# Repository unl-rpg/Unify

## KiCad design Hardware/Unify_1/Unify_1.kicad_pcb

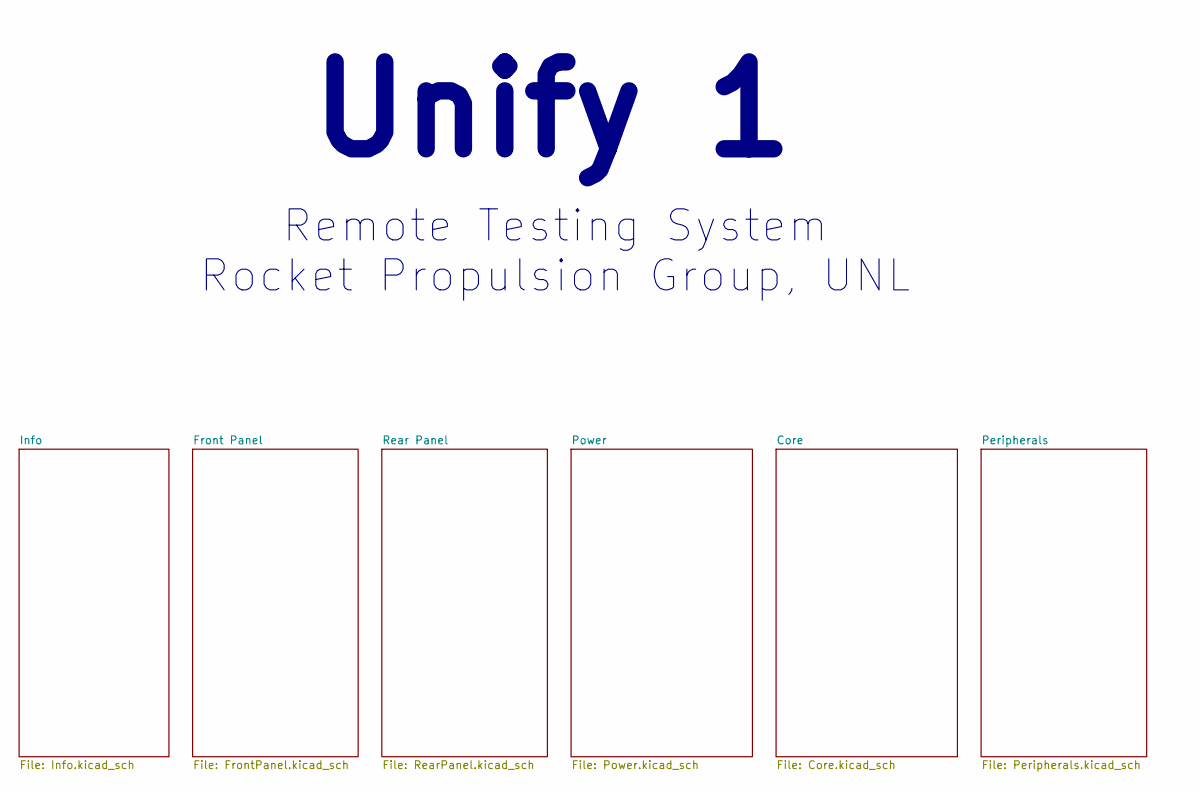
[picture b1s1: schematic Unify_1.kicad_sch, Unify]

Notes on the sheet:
Unify 1
Remote Testing System Rocket Propulsion Group, UNL

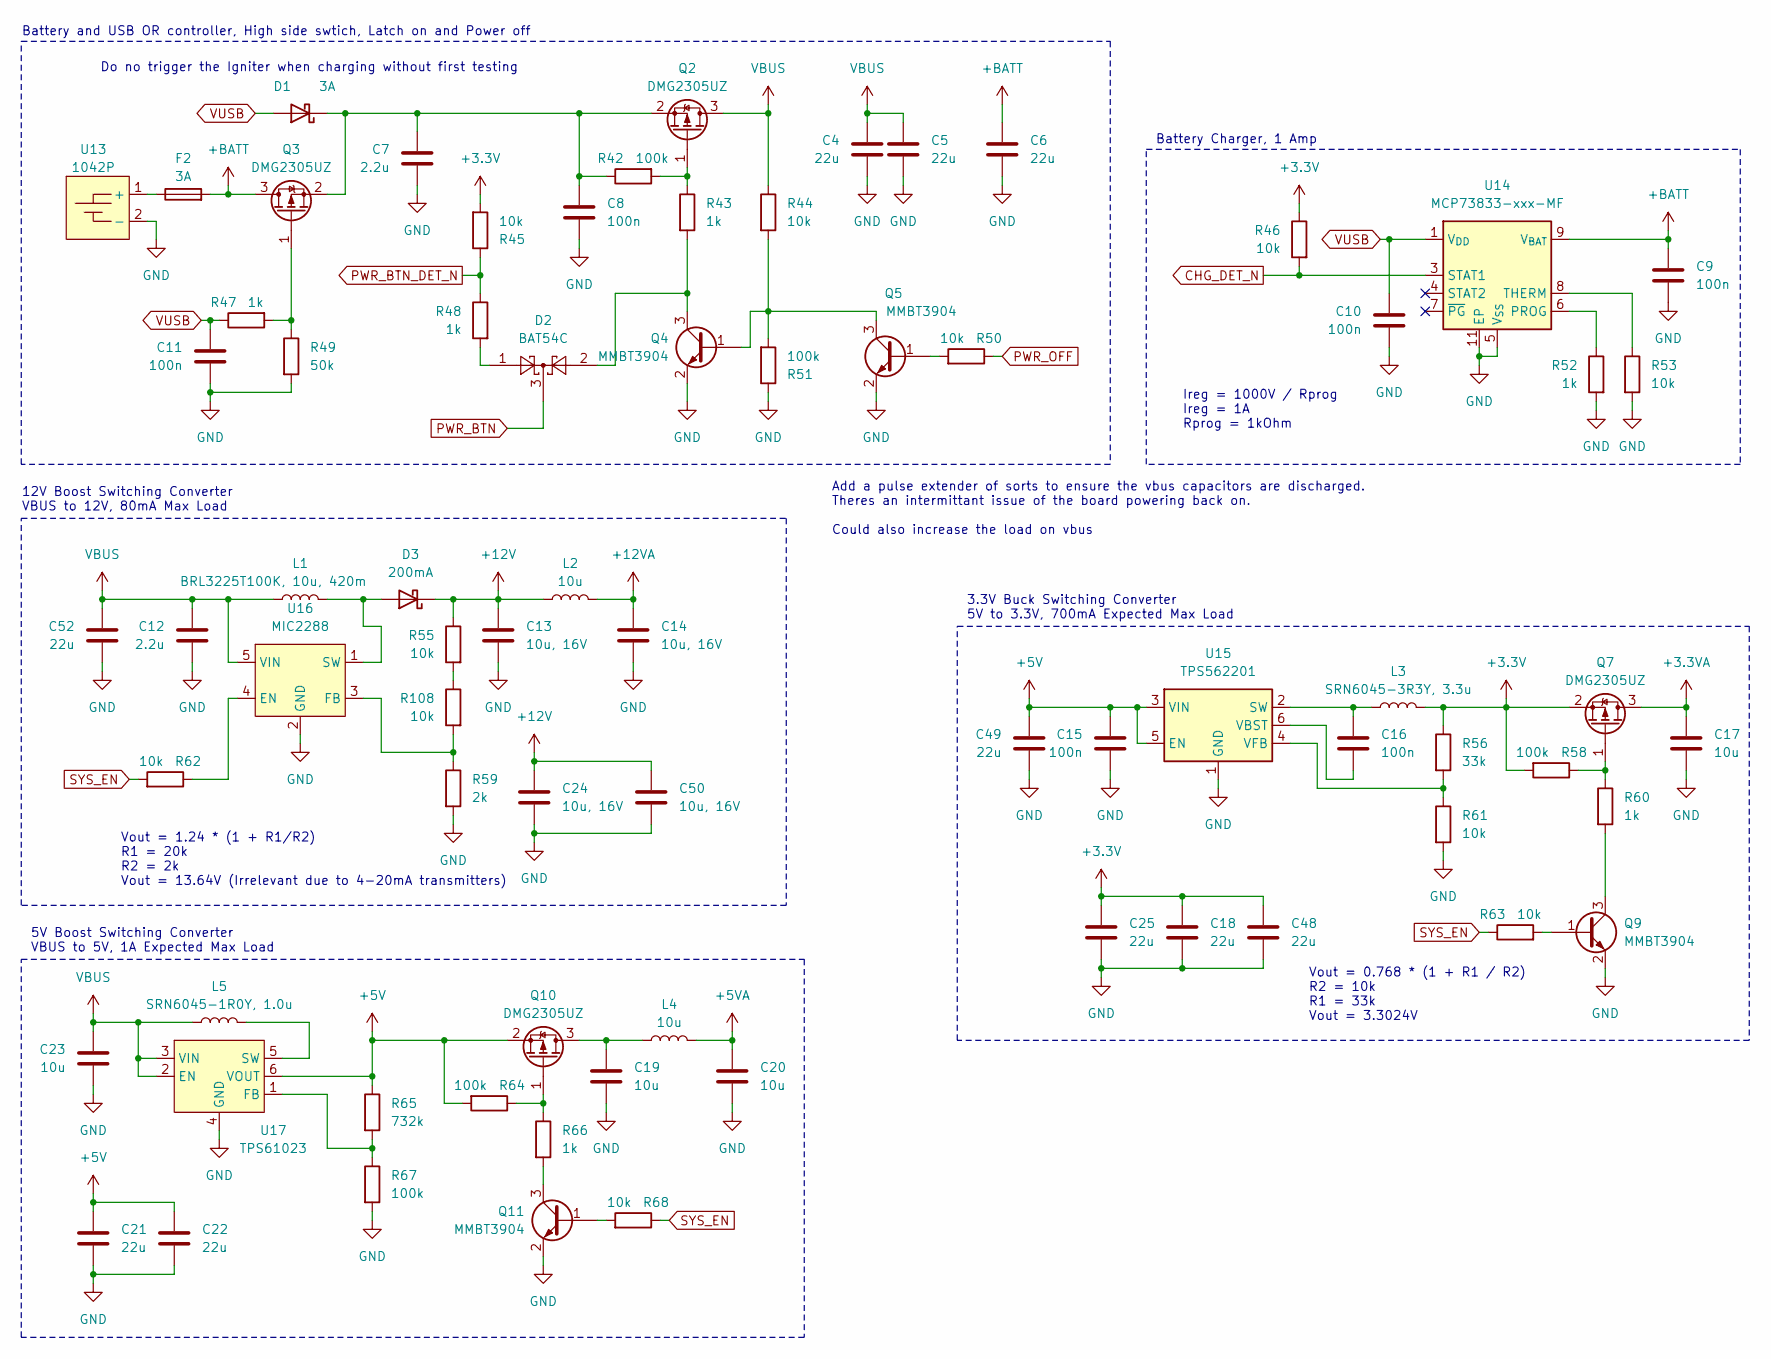
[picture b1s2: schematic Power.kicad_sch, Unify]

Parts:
C4, C5, C6, C18, C21, C22, C25, C48, C49, C52: 22u; C_0603_1608Metric
C7, C12: 2.2u; C_0603_1608Metric
C8, C9, C10, C11, C15, C16: 100n; C_0603_1608Metric
C13, C14, C24, C50: 10u, 16V; C_0603_1608Metric
C17, C19, C20, C23: 10u; C_0603_1608Metric
D1: 3A; D_SMA
D2: BAT54C; SOT-23
D3: 200mA; D_SOD-323
F2: 3A; Fuse_1206_3216Metric
L1: BRL3225T100K, 10u, 420m; L_1210_3225Metric
L2, L4: 10u; L_0805_2012Metric
L3: SRN6045-3R3Y, 3.3u; IND_BOURNS_SRN6045
L5: SRN6045-1R0Y, 1.0u; IND_BOURNS_SRN6045
Q2, Q3, Q7, Q10: DMG2305UZ; SOT-23
Q4, Q5, Q9, Q11: MMBT3904; SOT-23
R42, R51, R58, R64, R67: 100k; R_0603_1608Metric
R43, R47, R48, R52, R60, R66: 1k; R_0603_1608Metric
R44, R45, R46, R50, R53, R55, R61, R62, R63, R68, R108: 10k; R_0603_1608Metric
R49: 50k; R_0603_1608Metric
R56: 33k; R_0603_1608Metric
R59: 2k; R_0603_1608Metric
R65: 732k; R_0603_1608Metric
U13: 1042P; BAT_1042P
U14: MCP73833-xxx-MF; DFN-10-1EP_3x3mm_P0.5mm_EP1.58x2.35mm
U15: TPS562201; SOT-23-6
U16: MIC2288; TSOT-23-5
U17: TPS61023; SOT-563

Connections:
+5V: C15.1, C21.1, C22.1, C49.1, Q10.2 (S), R64.2, R65.1, U15.3 (VIN), U15.5 (EN), U17.6 (VOUT); also elsewhere on the board
+5VA: C20.1, L4.2; also elsewhere on the board
+12V: C13.1, C24.1, C50.1, D3.1 (K), L2.1, R55.1
+12VA: C14.1, L2.2; also elsewhere on the board
+BATT: C6.1, C9.1, F2.2, Q3.3 (D), U14.9 (V_{BAT}), U14.10 (V_{BAT}); also elsewhere on the board
CHG_DET_N: R46.2, U14.3 (STAT1); also elsewhere on the board
GND: C4.2, C5.2, C6.2, C7.2, C8.2, C9.2, C10.2, C11.2, C12.2, C13.2, C14.2, C15.2, C17.2, C18.2, C19.2, C20.2, C21.2, C22.2, C23.2, C24.2, C25.2, C48.2, C49.2, C50.2, C52.2, Q4.2 (E), Q5.2 (E), Q9.2 (E), Q11.2 (E), R49.2, R51.1, R52.2, R53.2, R59.2, R61.2, R67.2, U13.2 (-), U14.5 (V_{SS}), U14.11 (EP), U15.1 (GND), U16.2 (GND), U17.4 (GND); also elsewhere on the board
unnamed: C7.1, C8.1, D1.1 (K), Q2.2 (S), Q3.2 (S), R42.1
unnamed: D2.1, R48.2
unnamed: D3.2 (A), L1.2, U16.1 (SW)
unnamed: Q2.1 (G), R42.2, R43.1
unnamed: Q3.1 (G), R47.2, R49.1
unnamed: Q4.1 (B), Q5.3 (C), R44.2, R51.2
unnamed: D2.2, Q4.3 (C), R43.2
unnamed: Q5.1 (B), R50.2
unnamed: Q7.1 (G), R58.1, R60.1
unnamed: Q9.1 (B), R63.2
unnamed: Q9.3 (C), R60.2
unnamed: C19.1, L4.1, Q10.3 (D)
unnamed: Q10.1 (G), R64.1, R66.1
unnamed: Q11.1 (B), R68.2
unnamed: Q11.3 (C), R66.2
unnamed: R55.2, R108.1
unnamed: F2.1, U13.1 (+)
unnamed: R52.1, U14.6 (PROG)
unnamed: R53.1, U14.8 (THERM)
unnamed: C16.1, L3.1, U15.2 (SW)
unnamed: C16.2, U15.6 (VBST)
unnamed: R56.2, R61.1, U15.4 (VFB)
unnamed: R59.1, R108.2, U16.3 (FB)
unnamed: R65.2, R67.1, U17.1 (FB)
unnamed: L5.2, U17.5 (SW)
PWR_BTN: D2.3; also elsewhere on the board
PWR_BTN_DET_N: R45.1, R48.1; also elsewhere on the board
PWR_OFF: R50.1; also elsewhere on the board
VUSB: C10.1, C11.1, D1.2 (A), R47.1, U14.1 (V_{DD}), U14.2 (V_{DD}); also elsewhere on the board

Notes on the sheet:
Add a pulse extender of sorts to ensure the vbus capacitors are discharged. Theres an intermittant issue of the board powering back on. Could also increase the load on vbus
5V Boost Switching Converter VBUS to 5V, 1A Expected Max Load
Vout = 1.24 * (1 + R1/R2) R1 = 20k R2 = 2k Vout = 13.64V (Irrelevant due to 4-20mA transmitters)
3.3V Buck Switching Converter 5V to 3.3V, 700mA Expected Max Load
Battery and USB OR controller, High side swtich, Latch on and Power off
Battery Charger, 1 Amp
Ireg = 1000V / Rprog Ireg = 1A Rprog = 1kOhm
Do no trigger the Igniter when charging without first testing
Vout = 0.768 * (1 + R1 / R2) R2 = 10k R1 = 33k Vout = 3.3024V
12V Boost Switching Converter VBUS to 12V, 80mA Max Load

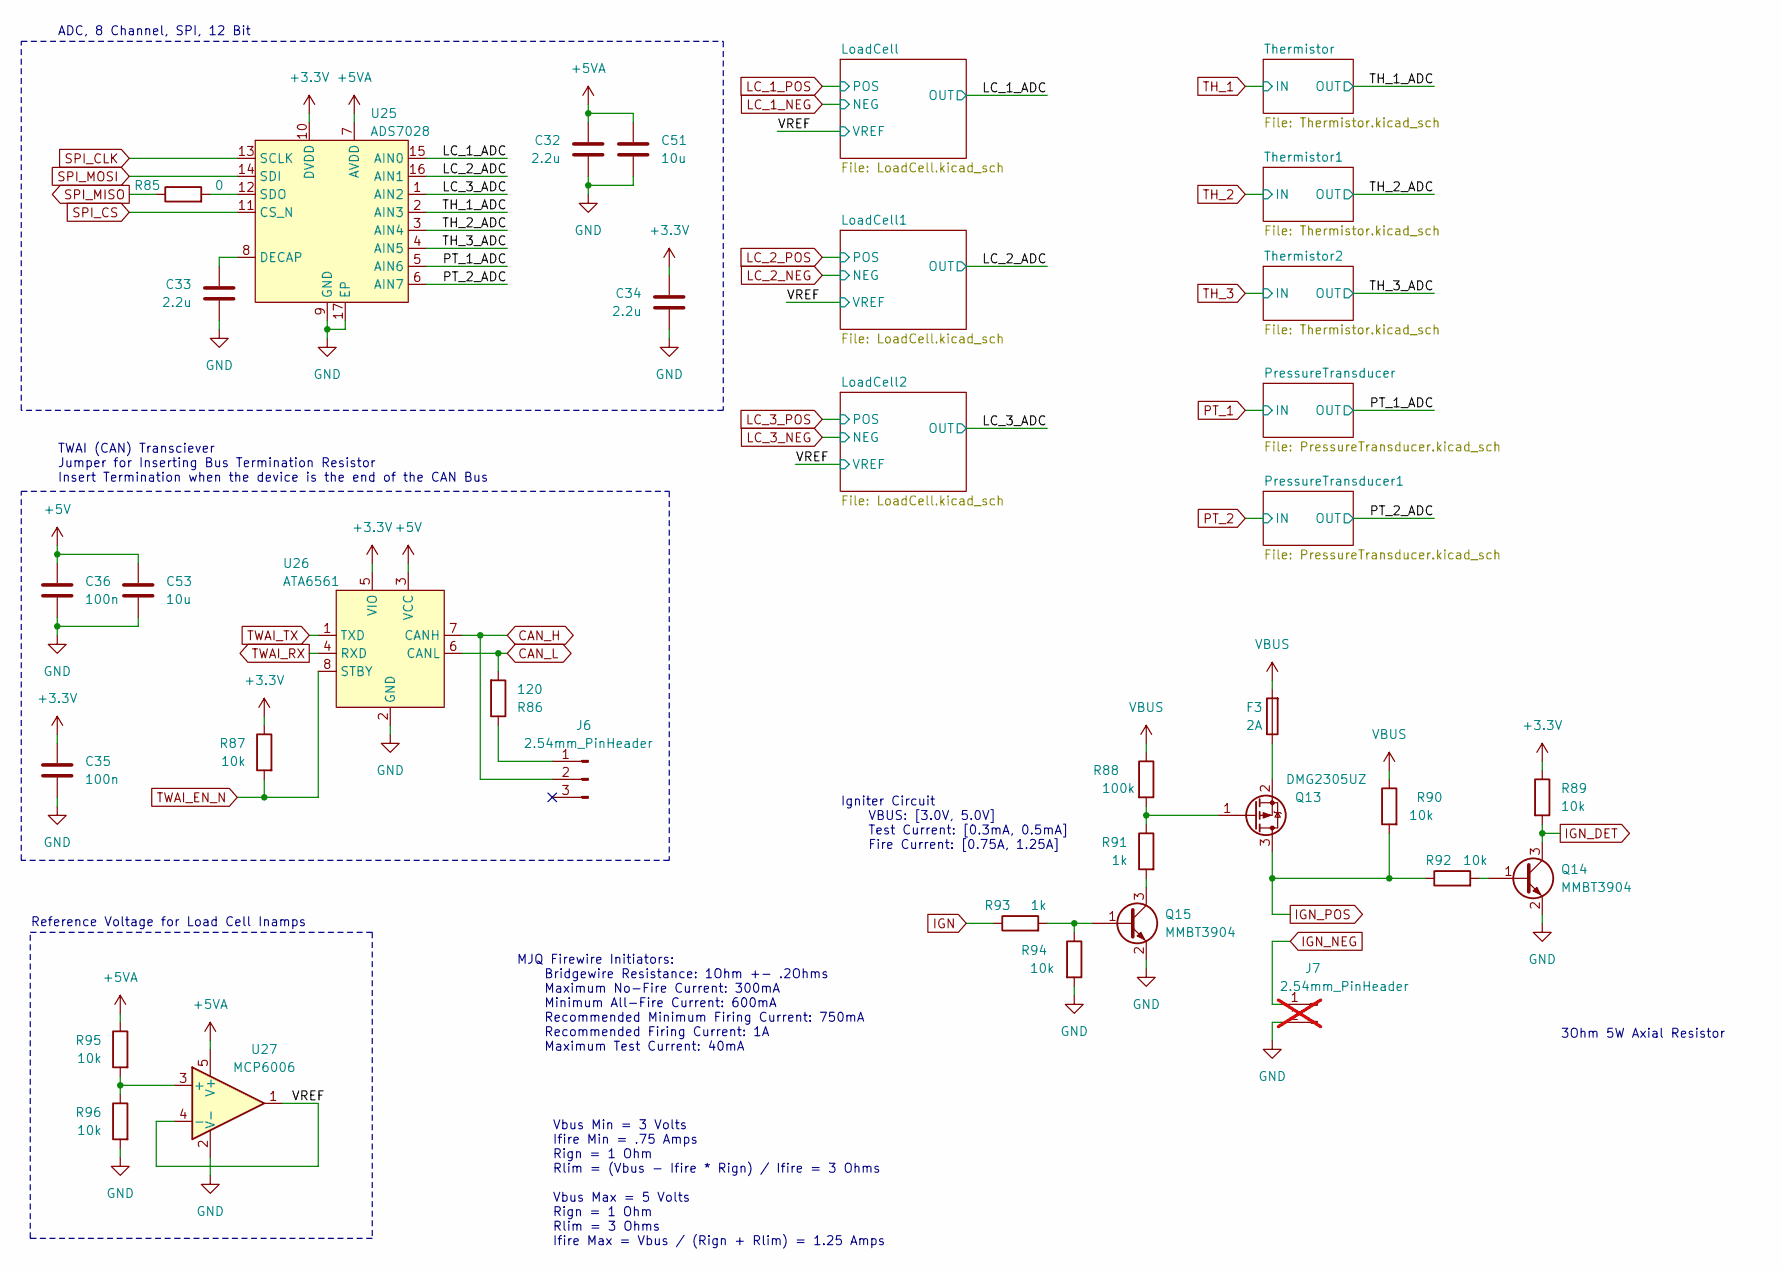
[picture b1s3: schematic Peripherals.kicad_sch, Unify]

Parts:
C32, C33, C34: 2.2u; C_0603_1608Metric
C35, C36: 100n; C_0603_1608Metric
C51, C53: 10u; C_0603_1608Metric
F3: 2A; Fuse_1206_3216Metric
J6: 2.54mm_PinHeader; PinHeader_1x03_P2.54mm_Vertical
J7: 2.54mm_PinHeader; PinHeader_1x02_P2.54mm_Vertical; not fitted
Q13: DMG2305UZ; SOT-23
Q14, Q15: MMBT3904; SOT-23
R85: 0; R_0603_1608Metric
R86: 120; R_0603_1608Metric
R87, R89, R90, R92, R94, R95, R96: 10k; R_0603_1608Metric
R88: 100k; R_0603_1608Metric
R91, R93: 1k; R_0603_1608Metric
U25: ADS7028; WQFN-16-1EP_3x3mm_P0.5mm_EP1.68x1.68mm
U26: ATA6561; SOIC-8_3.9x4.9mm_P1.27mm
U27: MCP6006; SOT-23-5

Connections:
+5V: C36.1, C53.1, U26.3 (VCC); also elsewhere on the board
+5VA: C32.1, C51.1, R95.1, U25.7 (AVDD), U27.5 (V+); also elsewhere on the board
/Peripherals/LC_1_ADC: U25.15 (AIN0); also elsewhere on the board
/Peripherals/LC_2_ADC: U25.16 (AIN1); also elsewhere on the board
/Peripherals/LC_3_ADC: U25.1 (AIN2); also elsewhere on the board
/Peripherals/VREF: U27.1, U27.4 (-); also elsewhere on the board
CAN_H: J6.2, U26.7 (CANH); also elsewhere on the board
CAN_L: R86.2, U26.6 (CANL); also elsewhere on the board
GND: C32.2, C33.2, C34.2, C35.2, C36.2, C51.2, C53.2, J7.2, Q14.2 (E), Q15.2 (E), R94.2, R96.2, U25.9 (GND), U25.17 (EP), U26.2 (GND), U27.2 (V-); also elsewhere on the board
IGN: R93.1; also elsewhere on the board
IGN_DET: Q14.3 (C), R89.2; also elsewhere on the board
IGN_NEG: J7.1; also elsewhere on the board
IGN_POS: Q13.3 (D), R90.2, R92.1; also elsewhere on the board
unnamed: J6.1, R86.1
unnamed: Q13.1 (G), R88.2, R91.1
unnamed: F3.1, Q13.2 (S)
unnamed: Q14.1 (B), R92.2
unnamed: Q15.1 (B), R93.2, R94.1
unnamed: Q15.3 (C), R91.2
unnamed: C33.1, U25.8 (DECAP)
unnamed: R85.2, U25.12 (SDO)
unnamed: R95.2, R96.1, U27.3 (+)
PT_1: U25.5 (AIN6); also elsewhere on the board
PT_2: U25.6 (AIN7); also elsewhere on the board
SPI_MISO: R85.1; also elsewhere on the board
SPI_MOSI: U25.14 (SDI); also elsewhere on the board
TH_1: U25.2 (AIN3); also elsewhere on the board
TH_2: U25.3 (AIN4); also elsewhere on the board
TH_3: U25.4 (AIN5); also elsewhere on the board
TWAI_EN_N: R87.2, U26.8 (STBY); also elsewhere on the board
TWAI_RX: U26.4 (RXD); also elsewhere on the board
TWAI_TX: U26.1 (TXD); also elsewhere on the board

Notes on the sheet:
Reference Voltage for Load Cell Inamps
MJQ Firewire Initiators: Bridgewire Resistance: 1Ohm +- .2Ohms Maximum No-Fire Current: 300mA Minimum All-Fire Current: 600mA Recommended Minimum Firing Current: 750mA Recommended Firing Current: 1A Maximum Test Current: 40mA
TWAI (CAN) Transciever Jumper for Inserting Bus Termination Resistor Insert Termination when the device is the end of the CAN Bus
ADC, 8 Channel, SPI, 12 Bit
Vbus Min = 3 Volts Ifire Min = .75 Amps Rign = 1 Ohm Rlim = (Vbus - Ifire * Rign) / Ifire = 3 Ohms Vbus Max = 5 Volts Rign = 1 Ohm Rlim = 3 Ohms Ifire Max = Vbus / (Rign + Rlim) = 1.25 Amps
3Ohm 5W Axial Resistor
Igniter Circuit VBUS: [3.0V, 5.0V] Test Current: [0.3mA, 0.5mA] Fire Current: [0.75A, 1.25A]

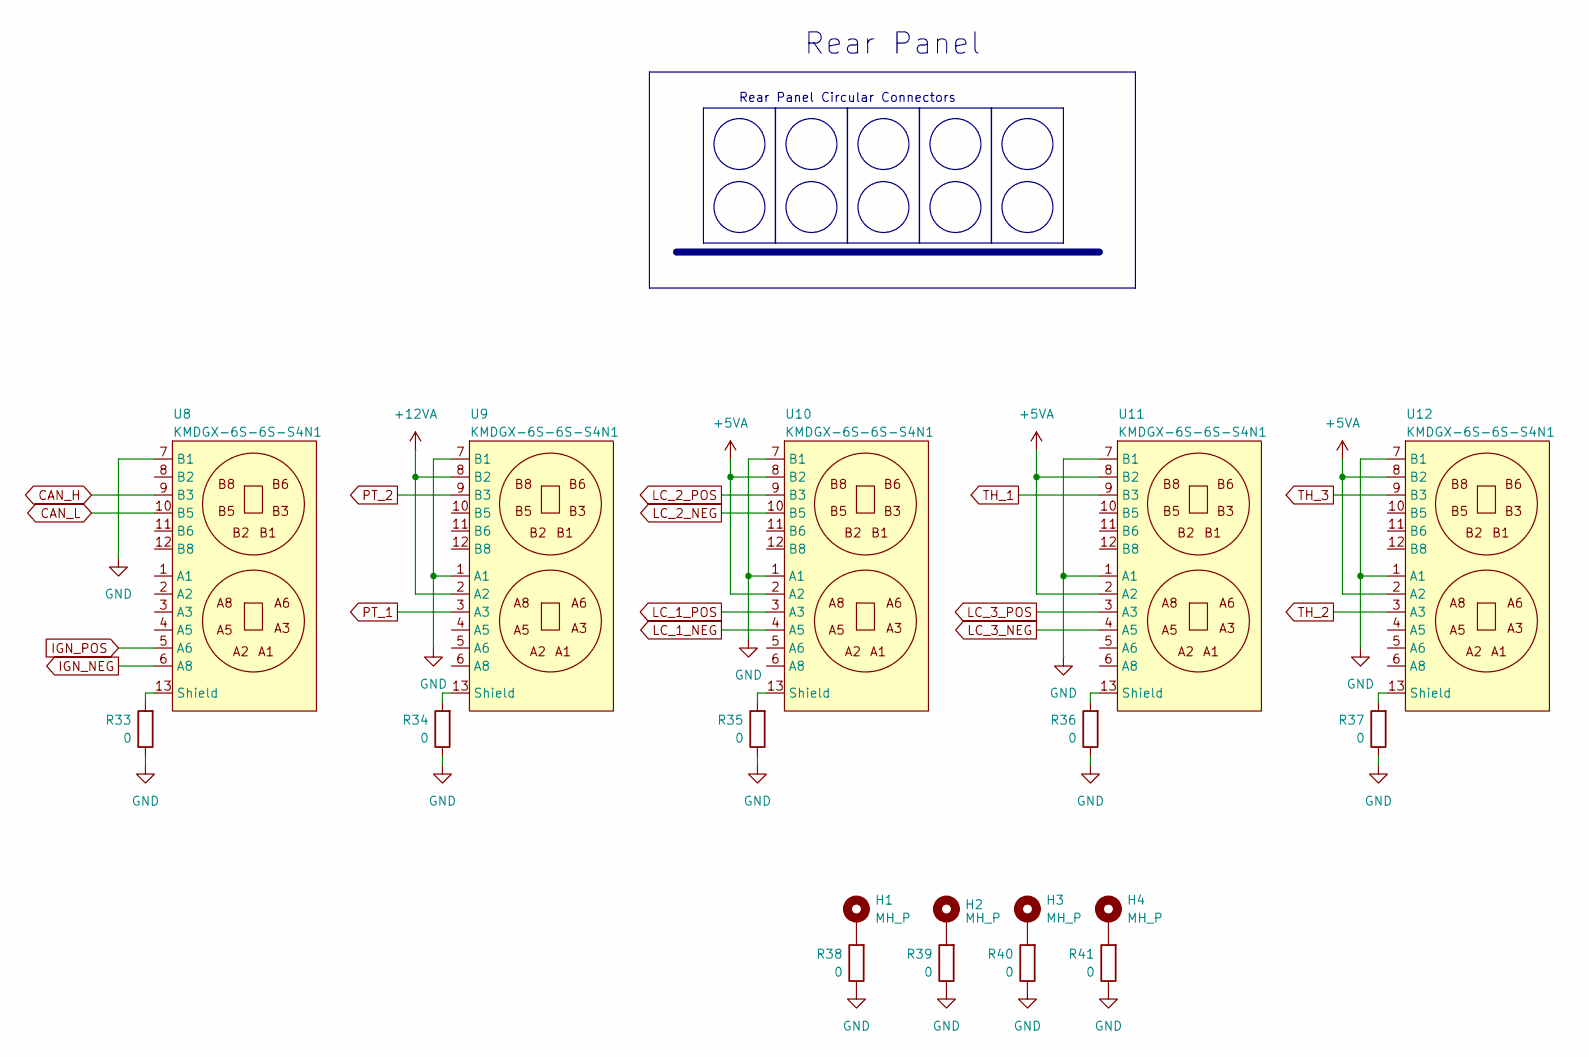
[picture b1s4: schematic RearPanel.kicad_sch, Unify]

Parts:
H1, H2, H3, H4: MH_P; MountingHole_2.7mm_M2.5_Pad
R33, R34, R35, R36, R37, R38, R39, R40, R41: 0; R_0603_1608Metric
U8, U9, U10, U11, U12: KMDGX-6S-6S-S4N1

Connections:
+5VA: U10.2 (A2), U10.8 (B2), U11.2 (A2), U11.8 (B2), U12.2 (A2), U12.8 (B2); also elsewhere on the board
+12VA: U9.2 (A2), U9.8 (B2); also elsewhere on the board
CAN_H: U8.9 (B3); also elsewhere on the board
CAN_L: U8.10 (B5); also elsewhere on the board
GND: R33.1, R34.1, R35.1, R36.1, R37.1, R38.1, R39.1, R40.1, R41.1, U8.7 (B1), U9.1 (A1), U9.7 (B1), U10.1 (A1), U10.7 (B1), U11.1 (A1), U11.7 (B1), U12.1 (A1), U12.7 (B1); also elsewhere on the board
IGN_NEG: U8.6 (A8); also elsewhere on the board
IGN_POS: U8.5 (A6); also elsewhere on the board
LC_1_NEG: U10.4 (A5); also elsewhere on the board
LC_1_POS: U10.3 (A3); also elsewhere on the board
LC_2_NEG: U10.10 (B5); also elsewhere on the board
LC_2_POS: U10.9 (B3); also elsewhere on the board
LC_3_NEG: U11.4 (A5); also elsewhere on the board
LC_3_POS: U11.3 (A3); also elsewhere on the board
unnamed: H1.1, R38.2
unnamed: H2.1, R39.2
unnamed: H3.1, R40.2
unnamed: H4.1, R41.2
unnamed: R33.2, U8.13 (Shield)
unnamed: R34.2, U9.13 (Shield)
unnamed: R35.2, U10.13 (Shield)
unnamed: R36.2, U11.13 (Shield)
unnamed: R37.2, U12.13 (Shield)
PT_1: U9.3 (A3); also elsewhere on the board
PT_2: U9.9 (B3); also elsewhere on the board
TH_1: U11.9 (B3); also elsewhere on the board
TH_2: U12.3 (A3); also elsewhere on the board
TH_3: U12.9 (B3); also elsewhere on the board

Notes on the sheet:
Rear Panel Circular Connectors
Rear Panel

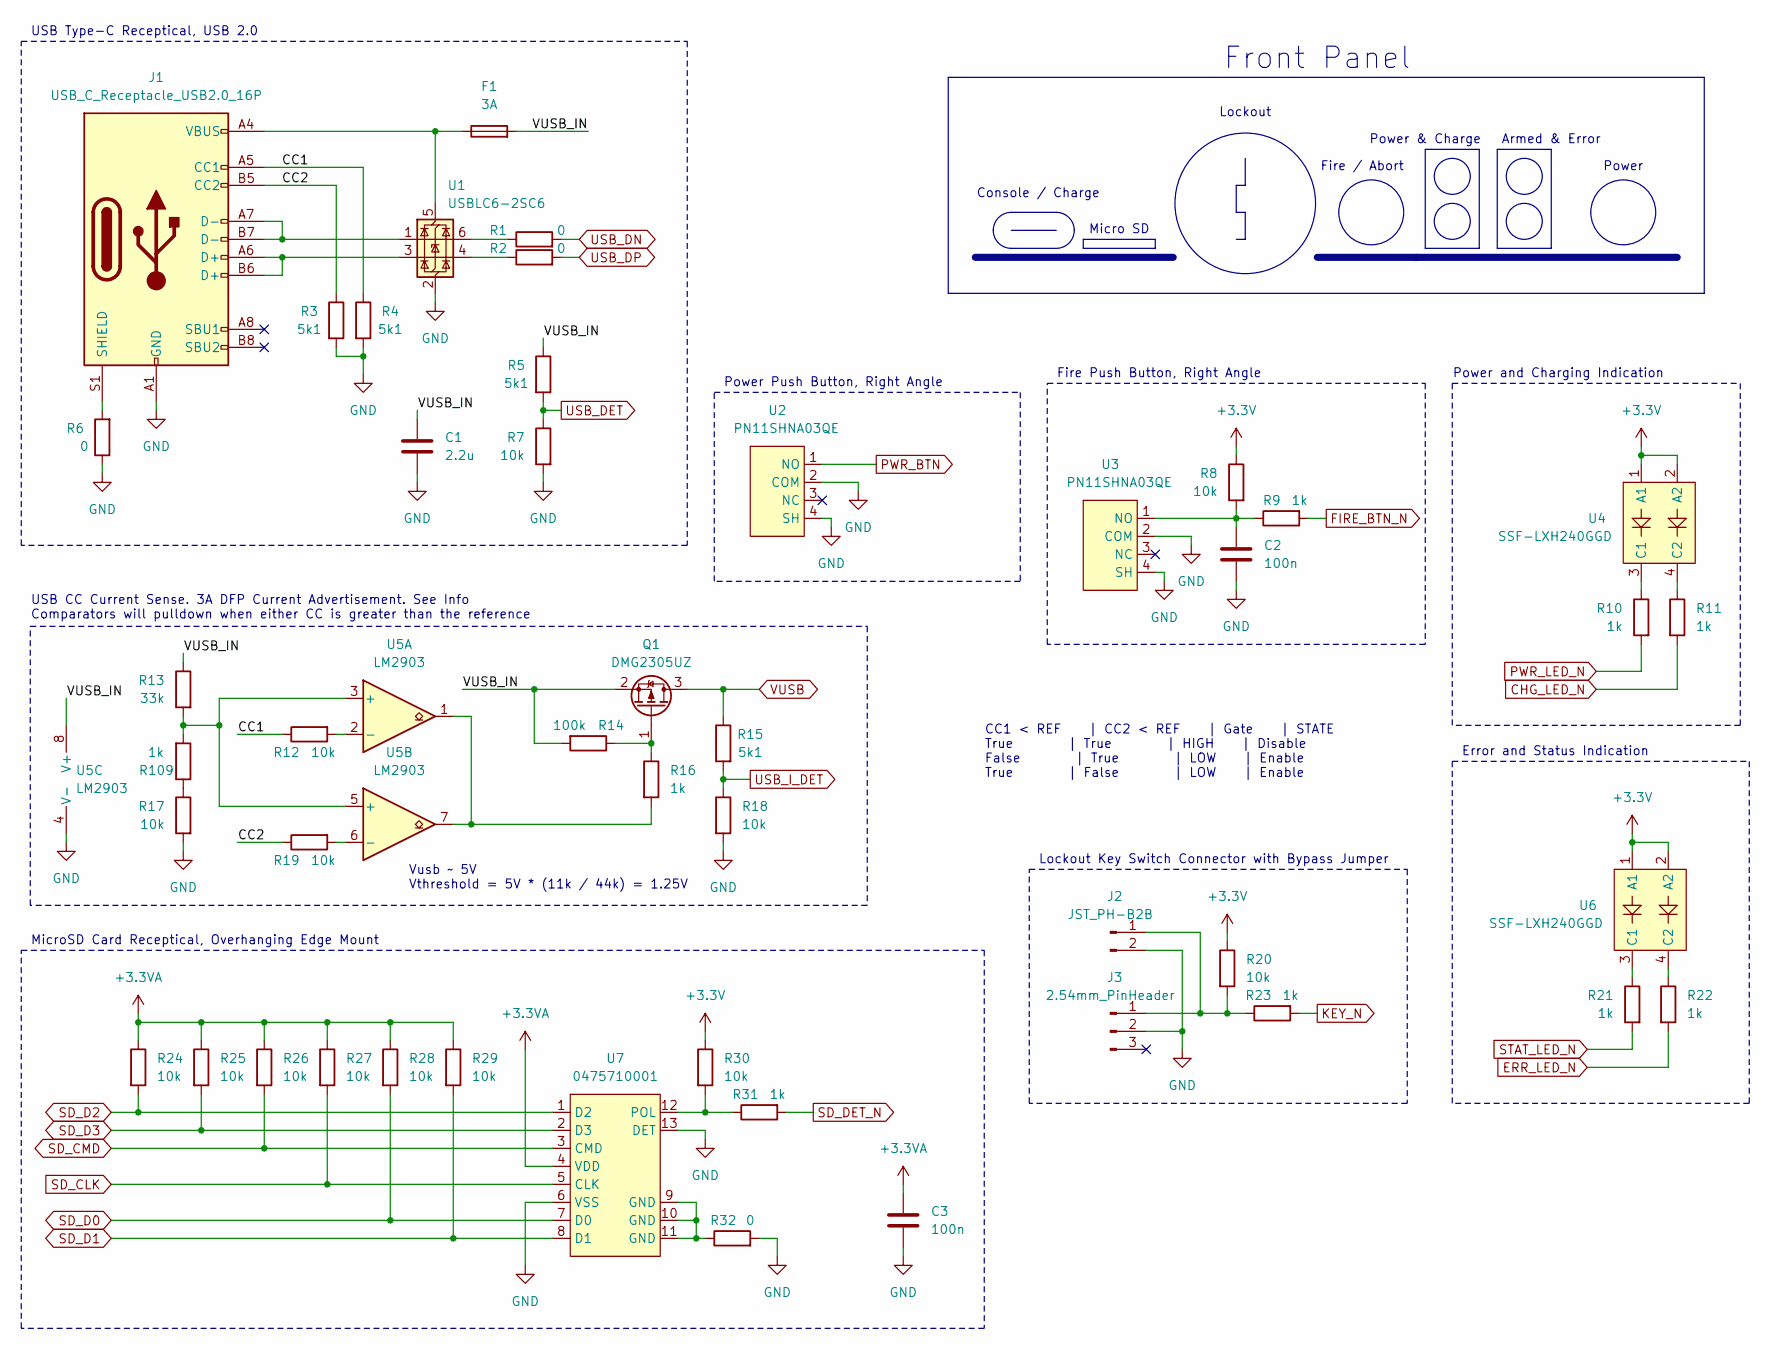
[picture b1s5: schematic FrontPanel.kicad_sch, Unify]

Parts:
C1: 2.2u; C_0603_1608Metric
C2, C3: 100n; C_0603_1608Metric
F1: 3A; Fuse_0603_1608Metric
J1: USB_C_Receptacle_USB2.0_16P; USB_C_Receptacle_GCT_USB4105-xx-A_16P_TopMnt_Horizontal
J2: JST_PH-B2B; JST_PH_B2B-PH-K_1x02_P2.00mm_Vertical
J3: 2.54mm_PinHeader; PinHeader_1x03_P2.54mm_Vertical
Q1: DMG2305UZ; SOT-23
R1, R2, R6, R32: 0; R_0603_1608Metric
R3, R4, R5, R15: 5k1; R_0603_1608Metric
R7, R8, R12, R17, R18, R19, R20, R24, R25, R26, R27, R28, R29, R30: 10k; R_0603_1608Metric
R9, R10, R11, R16, R21, R22, R23, R31, R109: 1k; R_0603_1608Metric
R13: 33k; R_0603_1608Metric
R14: 100k; R_0603_1608Metric
U1: USBLC6-2SC6; SOT-23-6
U2, U3: PN11SHNA03QE
U4, U6: SSF-LXH240GGD
U5: LM2903; SOIC-8_3.9x4.9mm_P1.27mm
U7: 0475710001; 47571-0001_MOL

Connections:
/Front Panel/CC1: J1.A5 (CC1), R4.1, R12.1
/Front Panel/CC2: J1.B5 (CC2), R3.1, R19.1
/Front Panel/VUSB_IN: C1.1, F1.2, Q1.2 (S), R5.1, R13.1, R14.2, U5.8 (V+)
CHG_LED_N: R11.2; also elsewhere on the board
ERR_LED_N: R22.2; also elsewhere on the board
FIRE_BTN_N: R9.2; also elsewhere on the board
GND: C1.2, C2.2, C3.2, J1.A1 (GND), J1.A12 (GND), J1.B1 (GND), J1.B12 (GND), J2.2, J3.2, R3.2, R4.2, R6.1, R7.2, R17.2, R18.2, R32.2, U1.2 (GND), U2.2 (COM), U2.4 (SH), U3.2 (COM), U3.4 (SH), U5.4 (V-), U7.6 (VSS), U7.13 (DET); also elsewhere on the board
KEY_N: R23.2; also elsewhere on the board
unnamed: J1.A6 (D+), J1.B6 (D+), U1.3 (I/O2)
unnamed: J1.A7 (D-), J1.B7 (D-), U1.1 (I/O1)
unnamed: J1.S1 (SHIELD), R6.2
unnamed: J2.1, J3.1, R20.2, R23.1
unnamed: Q1.1 (G), R14.1, R16.1
unnamed: R1.1, U1.6 (I/O1)
unnamed: R2.1, U1.4 (I/O2)
unnamed: R16.2, U5.1, U5.7
unnamed: R32.1, U7.9 (GND), U7.10 (GND), U7.11 (GND)
unnamed: R17.1, R109.1
unnamed: F1.1, J1.A4 (VBUS), J1.A9 (VBUS), J1.B4 (VBUS), J1.B9 (VBUS), U1.5 (VBUS)
unnamed: C2.1, R8.2, R9.1, U3.1 (NO)
unnamed: R10.1, U4.3 (C1)
unnamed: R11.1, U4.4 (C2)
unnamed: R13.2, R109.2, U5.3 (+), U5.5 (+)
unnamed: R12.2, U5.2 (-)
unnamed: R19.2, U5.6 (-)
unnamed: R21.1, U6.3 (C1)
unnamed: R22.1, U6.4 (C2)
unnamed: R30.2, R31.1, U7.12 (POL)
PWR_BTN: U2.1 (NO); also elsewhere on the board
PWR_LED_N: R10.2; also elsewhere on the board
SD_CLK: R27.2, U7.5 (CLK); also elsewhere on the board
SD_CMD: R26.2, U7.3 (CMD); also elsewhere on the board
SD_D0: R28.2, U7.7 (D0); also elsewhere on the board
SD_D1: R29.2, U7.8 (D1); also elsewhere on the board
SD_D2: R24.2, U7.1 (D2); also elsewhere on the board
SD_D3: R25.2, U7.2 (D3); also elsewhere on the board
SD_DET_N: R31.2; also elsewhere on the board
STAT_LED_N: R21.2; also elsewhere on the board
USB_DET: R5.2, R7.1; also elsewhere on the board
USB_DN: R1.2; also elsewhere on the board
USB_DP: R2.2; also elsewhere on the board
USB_I_DET: R15.2, R18.1; also elsewhere on the board
VUSB: Q1.3 (D), R15.1; also elsewhere on the board

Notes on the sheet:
Fire Push Button, Right Angle
Vusb ~ 5V Vthreshold = 5V * (11k / 44k) = 1.25V
MicroSD Card Receptical, Overhanging Edge Mount
USB Type-C Receptical, USB 2.0
Console / Charge
USB CC Current Sense. 3A DFP Current Advertisement. See Info Comparators will pulldown when either CC is greater than the reference
Micro SD
Error and Status Indication
Power
Armed & Error
Front Panel
CC1 < REF | CC2 < REF | Gate | STATE True | True | HIGH | Disable False | True | LOW | Enable True | False | LOW | Enable
Lockout Key Switch Connector with Bypass Jumper
Power and Charging Indication
Power Push Button, Right Angle
Lockout
Power & Charge
Fire / Abort

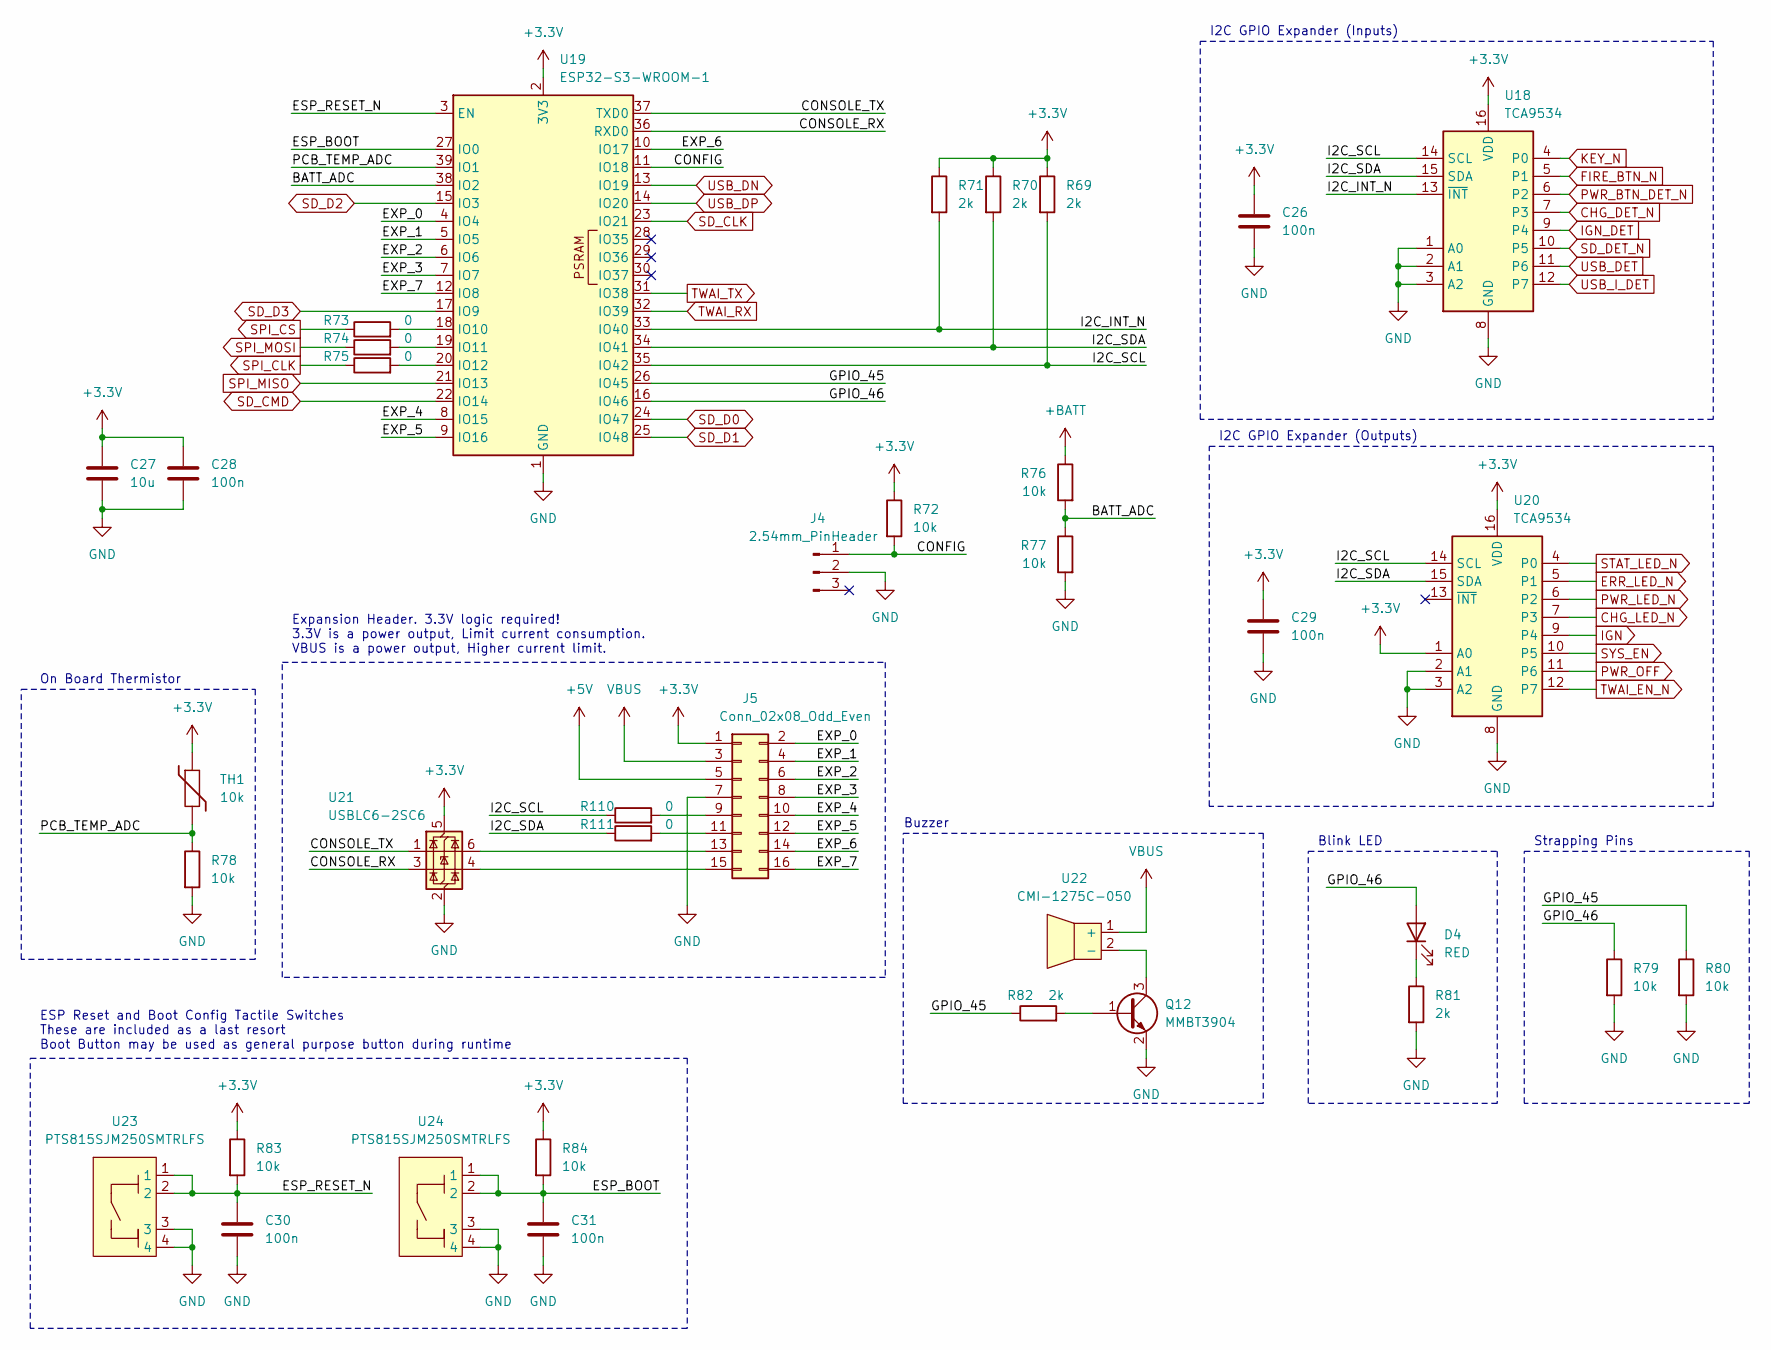
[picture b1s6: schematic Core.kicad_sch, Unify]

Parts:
C26, C28, C29, C30, C31: 100n; C_0603_1608Metric
C27: 10u; C_0603_1608Metric
D4: RED; LED_0603_1608Metric
J4: 2.54mm_PinHeader; PinHeader_1x03_P2.54mm_Vertical
J5: Conn_02x08_Odd_Even; PinHeader_2x08_P2.54mm_Vertical
Q12: MMBT3904; SOT-23
R69, R70, R71, R81, R82: 2k; R_0603_1608Metric
R72, R76, R77, R78, R79, R80, R83, R84: 10k; R_0603_1608Metric
R73, R74, R75, R110, R111: 0; R_0603_1608Metric
TH1: 10k; R_0603_1608Metric
U18, U20: TCA9534; TSSOP-16_4.4x5mm_P0.65mm
U19: ESP32-S3-WROOM-1; ESP32-S3-WROOM-1U
U21: USBLC6-2SC6; SOT-23-6
U22: CMI-1275C-050
U23, U24: PTS815SJM250SMTRLFS

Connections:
+5V: J5.5; also elsewhere on the board
+BATT: R76.1; also elsewhere on the board
/Core/BATT_ADC: R76.2, R77.1, U19.38 (IO2)
/Core/CONFIG: J4.1, R72.2, U19.11 (IO18)
/Core/CONSOLE_RX: U19.36 (RXD0), U21.3 (I/O2)
/Core/CONSOLE_TX: U19.37 (TXD0), U21.1 (I/O1)
/Core/ESP_BOOT: C31.1, R84.2, U19.27 (IO0), U24.1, U24.2
/Core/ESP_RESET_N: C30.1, R83.2, U19.3 (EN), U23.1, U23.2
/Core/EXP_0: J5.2, U19.4 (IO4)
/Core/EXP_1: J5.4, U19.5 (IO5)
/Core/EXP_2: J5.6, U19.6 (IO6)
/Core/EXP_3: J5.8, U19.7 (IO7)
/Core/EXP_4: J5.10, U19.8 (IO15)
/Core/EXP_5: J5.12, U19.9 (IO16)
/Core/EXP_6: J5.14, U19.10 (IO17)
/Core/EXP_7: J5.16, U19.12 (IO8)
/Core/GPIO_45: R80.1, R82.1, U19.26 (IO45)
/Core/GPIO_46: D4.2 (A), R79.1, U19.16 (IO46)
/Core/I2C_INT_N: R71.2, U18.13 (~INT), U19.33 (IO40)
/Core/I2C_SCL: R69.2, R110.1, U18.14 (SCL), U19.35 (IO42), U20.14 (SCL)
/Core/I2C_SDA: R70.2, R111.1, U18.15 (SDA), U19.34 (IO41), U20.15 (SDA)
/Core/PCB_TEMP_ADC: R78.1, TH1.2, U19.39 (IO1)
CHG_DET_N: U18.7 (P3); also elsewhere on the board
CHG_LED_N: U20.7 (P3); also elsewhere on the board
ERR_LED_N: U20.5 (P1); also elsewhere on the board
FIRE_BTN_N: U18.5 (P1); also elsewhere on the board
GND: C26.2, C27.2, C28.2, C29.2, C30.2, C31.2, J4.2, J5.7, Q12.2 (E), R77.2, R78.2, R79.2, R80.2, R81.2, U18.1 (A0), U18.2 (A1), U18.3 (A2), U18.8 (GND), U19.1 (GND), U19.40 (GND), U19.41 (GND), U20.2 (A1), U20.3 (A2), U20.8 (GND), U21.2 (GND), U23.3, U23.4, U24.3, U24.4; also elsewhere on the board
IGN: U20.9 (P4); also elsewhere on the board
IGN_DET: U18.9 (P4); also elsewhere on the board
KEY_N: U18.4 (P0); also elsewhere on the board
unnamed: D4.1 (K), R81.1
unnamed: J5.9, R110.2
unnamed: J5.11, R111.2
unnamed: J5.13, U21.6 (I/O1)
unnamed: J5.15, U21.4 (I/O2)
unnamed: Q12.1 (B), R82.2
unnamed: Q12.3 (C), U22.2 (-)
unnamed: R73.2, U19.18 (IO10)
unnamed: R74.2, U19.19 (IO11)
unnamed: R75.2, U19.20 (IO12)
PWR_BTN_DET_N: U18.6 (P2); also elsewhere on the board
PWR_LED_N: U20.6 (P2); also elsewhere on the board
PWR_OFF: U20.11 (P6); also elsewhere on the board
SD_CLK: U19.23 (IO21); also elsewhere on the board
SD_CMD: U19.22 (IO14); also elsewhere on the board
SD_D0: U19.24 (IO47); also elsewhere on the board
SD_D1: U19.25 (IO48); also elsewhere on the board
SD_D2: U19.15 (IO3); also elsewhere on the board
SD_D3: U19.17 (IO9); also elsewhere on the board
SD_DET_N: U18.10 (P5); also elsewhere on the board
SPI_MISO: U19.21 (IO13); also elsewhere on the board
SPI_MOSI: R74.1; also elsewhere on the board
STAT_LED_N: U20.4 (P0); also elsewhere on the board
TWAI_EN_N: U20.12 (P7); also elsewhere on the board
TWAI_RX: U19.32 (IO39); also elsewhere on the board
TWAI_TX: U19.31 (IO38); also elsewhere on the board
USB_DET: U18.11 (P6); also elsewhere on the board
USB_DN: U19.13 (IO19); also elsewhere on the board
USB_DP: U19.14 (IO20); also elsewhere on the board
USB_I_DET: U18.12 (P7); also elsewhere on the board

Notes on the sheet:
On Board Thermistor
Strapping Pins
Expansion Header. 3.3V logic required! 3.3V is a power output, Limit current consumption. VBUS is a power output, Higher current limit.
Buzzer
ESP Reset and Boot Config Tactile Switches These are included as a last resort Boot Button may be used as general purpose button during runtime
I2C GPIO Expander (Outputs)
I2C GPIO Expander (Inputs)
Blink LED

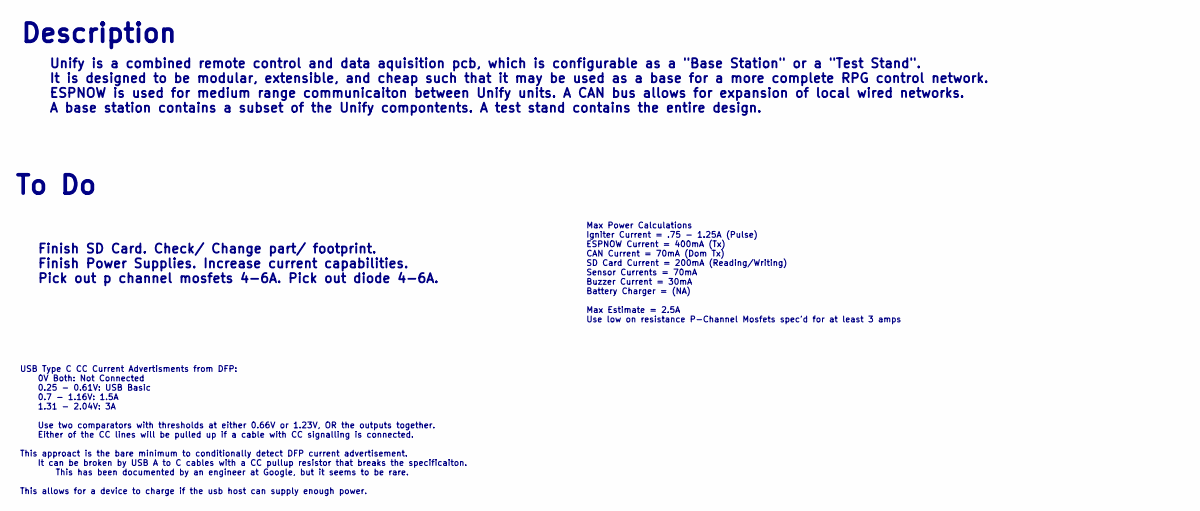
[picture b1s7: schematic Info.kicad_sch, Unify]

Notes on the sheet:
Max Power Calculations Igniter Current = .75 - 1.25A (Pulse) ESPNOW Current = 400mA (Tx) CAN Current = 70mA (Dom Tx) SD Card Current = 200mA (Reading/Writing) Sensor Currents = 70mA Buzzer Current = 30mA Battery Charger = (NA) Max Estimate = 2.5A Use low on resistance P-Channel Mosfets spec'd for a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
To Do
Finish SD Card. Check/ Change part/ footprint. Finish Power Supplies. Increase current capabilities. Pick out p channel mosfets 4-6A. Pick out diode 4-6A.
USB Type C CC Current Advertisments from DFP: 0V Both: Not Connected 0.25 - 0.61V: USB Basic 0.7 - 1.16V: 1.5A 1.31 - 2.04V: 3A Use two comparators with thresholds at either 0.66V or 1.23V, OR the outputs together. Either of the CC lines will be pulled up if a cable with CC signalling is connected.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
Unify is a combined remote control and data aquisition pcb, which is configurable as a "Base Station" or a "Test Stand". It is designed to be modular, extensible, and cheap such that it may be used as a base for a more complete RPG control network. ESPNOW is used for medium range communicaiton betw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
Description

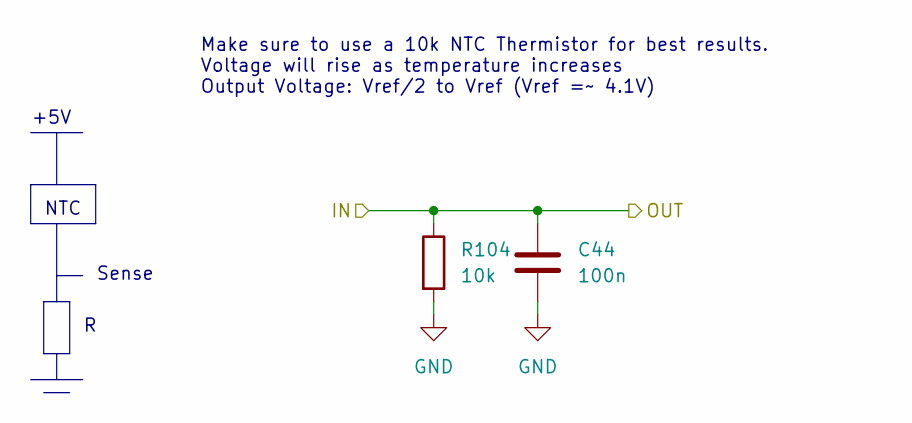
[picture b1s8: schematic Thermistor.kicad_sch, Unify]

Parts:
C44: 100n; C_0603_1608Metric
R104: 10k; R_0603_1608Metric

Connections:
GND: C44.2, R104.2; also elsewhere on the board
TH_2: C44.1, R104.1; also elsewhere on the board

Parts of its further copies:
C43, C45: 100n; C_0603_1608Metric
R103, R105: 10k; R_0603_1608Metric

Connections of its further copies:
GND: C43.2, C45.2, R103.2, R105.2; also elsewhere on the board
TH_1: C43.1, R103.1; also elsewhere on the board
TH_3: C45.1, R105.1; also elsewhere on the board

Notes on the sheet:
Make sure to use a 10k NTC Thermistor for best results. Voltage will rise as temperature increases Output Voltage: Vref/2 to Vref (Vref =~ 4.1V)
Sense
+5V
NTC
